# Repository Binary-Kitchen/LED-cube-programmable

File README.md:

# Programmable LED Cube
A 4x4x4 LED Cube which can be programmed with an arduino nano. A harder soldering challenge combining SMD soldering with very fragile LEDs.

## Bill of Material
| Item                     | Qty | Footprint          |
|--------------------------|-----|--------------------|
| Arduino Nano v3          | 1   | ----               |
| Ceramic Capacitor 100 nF | 1   | 0805               |
| Mosfet 2N7002            | 4   | SOT23              |
| Resistor 1 kOhm          | 4   |  0805              |
| Resistor 52 Ohm          | 16  | 0805               |
| Shiftregister 74HC595    | 2   | SOIC-16 3.9x9.9 mm |
| 5mm LED                  | 64  | ----               |

## Manual
TBD

## Copyright and Authorship
- Idea/PCB-Layout: [CC-BY-SA 4.0](https://creativecommons.org/licenses/by-sa/4.0/) - [Thomas Schmid and Timo Schindler](https://www.binary-kitchen.de)
- Manual (TeX): [LPPL](https://www.latex-project.org/lppl.txt) - [Marei Peischl](https://peitex.de)
- Manual (pdf): [CC-BY-SA 4.0](https://creativecommons.org/licenses/by-sa/4.0/) - [Binary Kitchen e.V.](https://www.binary-kitchen.de)

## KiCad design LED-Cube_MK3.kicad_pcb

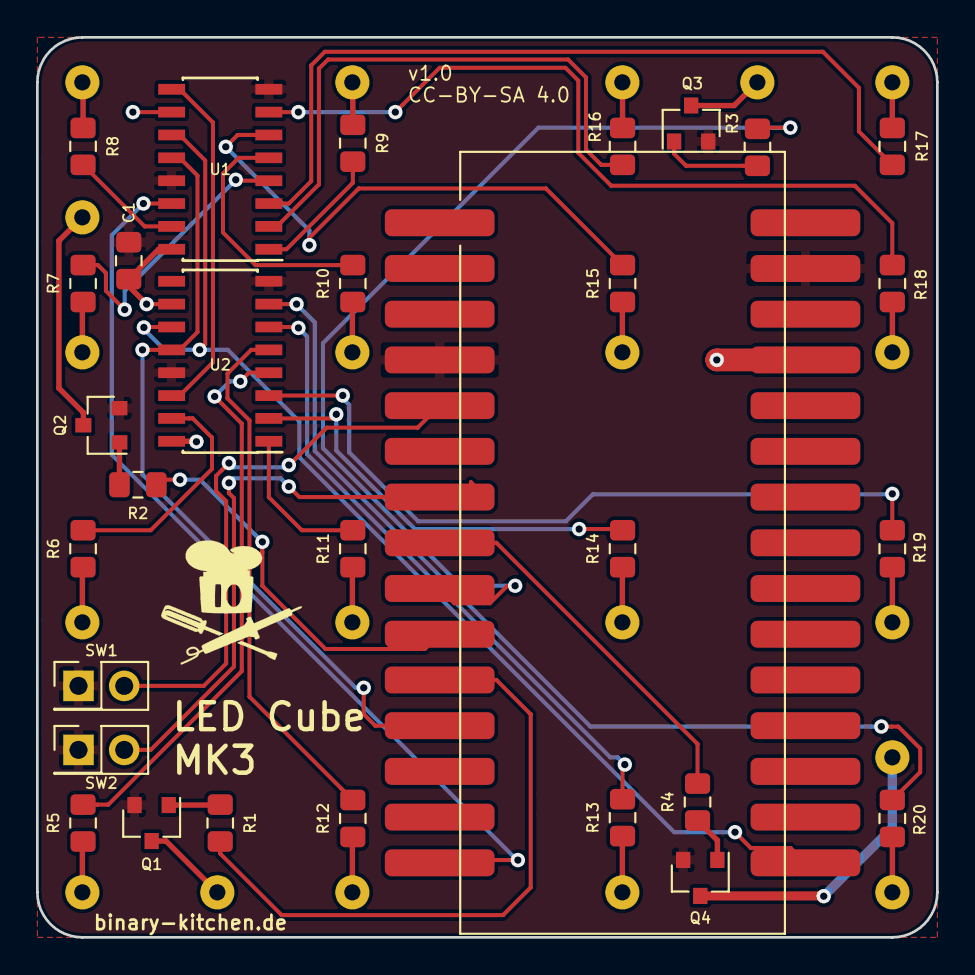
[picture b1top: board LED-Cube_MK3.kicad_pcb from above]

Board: 2 copper layers, 50.0 x 50.0 mm, 31 parts (1 on the bottom side), 52 nets.

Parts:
A1: Arduino_Nano_v3.x; Arduino_Nano_SMD
C1: C; C_0805_2012Metric_Pad1.15x1.40mm_HandSolder
Q1, Q2, Q3, Q4: 2N7002; SOT-23
R1, R2, R3, R4, R5, R6, R7, R8, R9, R10, R11, R12, R13, R14, R15, R16, R17, R18, R19, R20: R; R_0805_2012Metric_Pad1.15x1.40mm_HandSolder
SW1, SW2: SW_Push; PinHeader_2x01_P2.54mm_Vertical
U1, U2: 74HC595; SOIC-16_3.9x9.9mm_P1.27mm
U3: LED_Cube_5mm_4x4x4

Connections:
+5V: A1.27, C1.1, U1.10, U1.16, U2.10, U2.16
/QH*: U1.9, U2.14
/cathode1_enable: A1.8, R4.2
/cathode2_enable: A1.9, R3.2
/cathode3_enable: A1.10, R2.2
/cathode4_enable: A1.11, R1.2
/mode_sw: A1.7, SW2.2
/mosi: A1.15, U1.14
/power_sw: A1.5, SW1.2
/scrclk: A1.16, U1.11, U2.11
/sr_latch: A1.12, U1.12, U2.12
GND: A1.4, A1.29, C1.2, Q1.2, Q2.2, Q3.2, Q4.2, SW1.1, SW2.1, U1.8, U1.13, U2.8, U2.13
LED_1: R8.2, U1.15
LED_2: R9.2, U1.1
LED_3: R16.2, U1.2
LED_4: R17.2, U1.3
LED_5: R7.2, U1.4
LED_6: R10.2, U1.5
LED_7: R15.2, U1.6
LED_8: R18.2, U1.7
LED_9: R6.2, U2.15
LED_10: R11.2, U2.1
LED_11: R14.2, U2.2
LED_12: R19.2, U2.3
LED_13: R5.2, U2.4
LED_14: R12.2, U2.5
LED_15: R13.2, U2.6
LED_16: R20.2, U2.7
unnamed: Q1.1, R1.1
unnamed: Q1.3, U3.17
unnamed: Q2.1, R2.1
unnamed: Q2.3, U3.18
unnamed: Q3.1, R3.1
unnamed: Q3.3, U3.19
unnamed: Q4.1, R4.1
unnamed: Q4.3, U3.20
unnamed: R5.1, U3.1
unnamed: R6.1, U3.2
unnamed: R7.1, U3.3
unnamed: R8.1, U3.4
unnamed: R9.1, U3.5
unnamed: R10.1, U3.6
unnamed: R11.1, U3.7
unnamed: R12.1, U3.8
unnamed: R13.1, U3.9
unnamed: R14.1, U3.10
unnamed: R15.1, U3.11
unnamed: R16.1, U3.12
unnamed: R17.1, U3.13
unnamed: R18.1, U3.14
unnamed: R19.1, U3.15
unnamed: R20.1, U3.16

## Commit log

2018-11-05 inital commit
2018-11-06 change led spacing to 15mm and add arduino 3d model
2018-11-06 add 3d model of leds
2018-11-18 added svg and kitchen-head for printing on board
2018-11-18 added footprint
2018-11-18 added logo, copyright, name and version
2018-11-18 minor changes
2018-11-18 added gerber files
2018-12-06 added readme
2018-12-18 Add missing part values
2018-12-21 add first working prototype of firmware
2018-12-21 move firmware to a seperate repository and add it as a submodule
2018-12-21 add bill of material to readme
2019-05-11 Misspellings
